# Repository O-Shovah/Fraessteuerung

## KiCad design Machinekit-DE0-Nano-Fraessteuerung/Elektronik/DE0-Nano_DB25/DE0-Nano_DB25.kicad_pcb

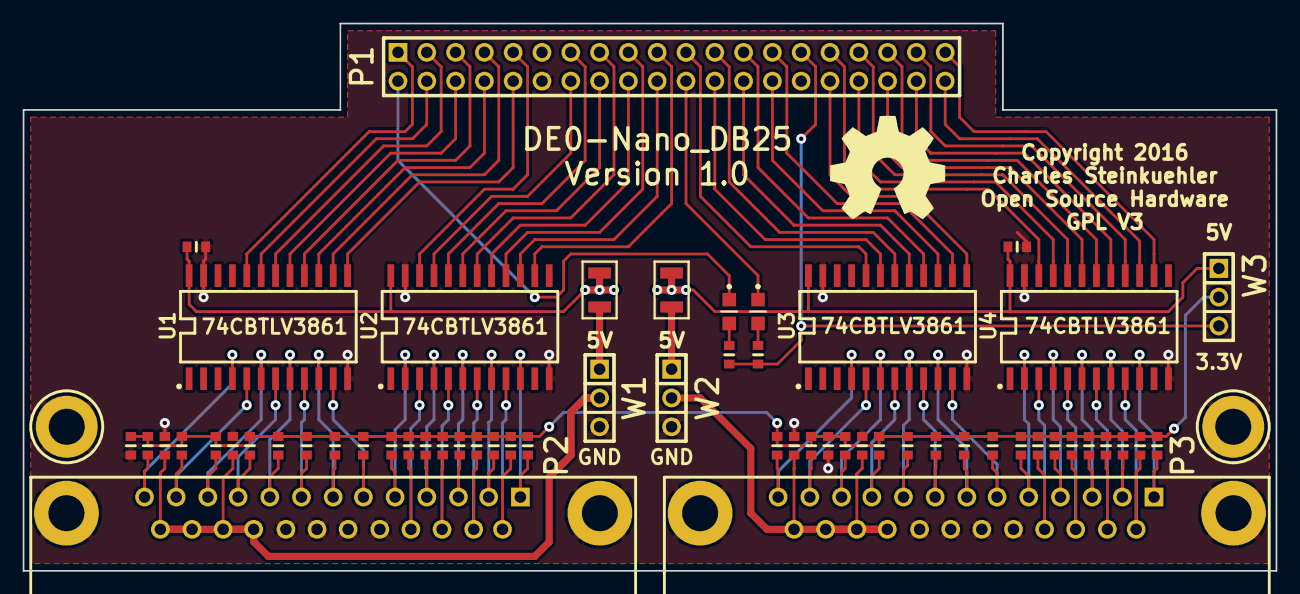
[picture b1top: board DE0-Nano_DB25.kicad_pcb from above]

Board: 2 copper layers, 110.5 x 48.3 mm, 63 parts (0 on the bottom side), 80 nets.

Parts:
C1, C2, C3, C4, C5, C6, C7, C8: 100n; CAPC1608x55N
LED1, LED2: Yellow; OSRAM-LED-0805
M1, M2: 4-40; MTH_4-40
P1: CONN_20X2; Pin_Socket_20x2
P2, P3: DB25; AMP-5747846
PTC1, PTC2: 2A; BOURNS-MF-NSMF
R1, R2, R3, R4, R5, R6, R7, R8, R9, R10, R11, R12, R13, R14, R15, R16, R17, R18, R19, R20, R21, R22, R23, R24, R25, R26, R27, R28, R29, R30, R31, R32, R33, R34: 3.3k; RESC1608x55N
R35, R36: 240R; RESC1608x55N
S1, S2, S3: SHUNT; Shunt
U1, U2, U3, U4: 74CBTLV3861; SOIC127P1030X265-24N
W1, W2, W3: HEADER_3; pin_strip_3

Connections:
+3.3V: P1.29, R35.1, R36.1, W3.3
+5V: C7.1, C8.1, P1.11, PTC1.2, PTC2.2, U1.24, U2.24, U3.24, U4.24, W3.1
/J1-0: P2.1, R1.2, U2.10
/J1-1: P2.14, R2.2, U2.9
/J1-2: P2.2, R3.2, U2.8
/J1-3: P2.15, R4.2, U2.7
/J1-4: P2.3, R5.2, U2.6
/J1-5: P2.16, R6.2, U2.5
/J1-6: P2.4, R7.2, U2.4
/J1-7: P2.17, R8.2, U2.3
/J1-8: P2.5, R9.2, U2.2
/J1-9: P2.6, R10.2, U1.11
/J1-10: P2.7, R11.2, U1.10
/J1-11: P2.8, R12.2, U1.9
/J1-12: P2.9, R13.2, U1.8
/J1-13: P2.10, R14.2, U1.7
/J1-14: P2.11, R15.2, U1.6
/J1-15: P2.12, R16.2, U1.5
/J1-16: P2.13, R17.2, U1.4
/J1-PWR: PTC1.1, W1.1
/J1B0: P1.19, U2.14
/J1B1: P1.20, U2.15
/J1B2: P1.17, U2.16
/J1B3: P1.18, U2.17
/J1B4: P1.15, U2.18
/J1B5: P1.16, U2.19
/J1B6: P1.13, U2.20
/J1B7: P1.14, U2.21
/J1B8: P1.9, U2.22
/J1B9: P1.10, U1.13
/J1B10: P1.7, U1.14
/J1B11: P1.8, U1.15
/J1B12: P1.5, U1.16
/J1B13: P1.6, U1.17
/J1B14: P1.3, U1.18
/J1B15: P1.4, U1.19
/J1B16: P1.1, U1.20
/J2-0: P3.1, R18.2, U4.10
/J2-1: P3.14, R19.2, U4.9
/J2-2: P3.2, R20.2, U4.8
/J2-3: P3.15, R21.2, U4.7
/J2-4: P3.3, R22.2, U4.6
/J2-5: P3.16, R23.2, U4.5
/J2-6: P3.4, R24.2, U4.4
/J2-7: P3.17, R25.2, U4.3
/J2-8: P3.5, R26.2, U4.2
/J2-9: P3.6, R27.2, U3.11
/J2-10: P3.7, R28.2, U3.10
/J2-11: P3.8, R29.2, U3.9
/J2-12: P3.9, R30.2, U3.8
/J2-13: P3.10, R31.2, U3.7
/J2-14: P3.11, R32.2, U3.6
/J2-15: P3.12, R33.2, U3.5
/J2-16: P3.13, R34.2, U3.4
/J2-PWR: PTC2.1, W2.1
/J2B0: P1.39, U4.14
/J2B1: P1.40, U4.15
/J2B2: P1.37, U4.16
/J2B3: P1.38, U4.17
/J2B4: P1.35, U4.18
/J2B5: P1.36, U4.19
/J2B6: P1.33, U4.20
/J2B7: P1.34, U4.21
/J2B8: P1.31, U4.22
/J2B9: P1.32, U3.13
/J2B10: P1.27, U3.14
/J2B11: P1.28, U3.15
/J2B12: P1.25, U3.16
/J2B13: P1.26, U3.17
/J2B14: P1.23, U3.18
/J2B15: P1.24, U3.19
/J2B16: P1.21, U3.20
/LED0: LED1.K, P1.2
/LED1: LED2.K, P1.22
/VPU: C5.1, C6.1, R1.1, R2.1, R3.1, R4.1, R5.1, R6.1, R7.1, R8.1, R9.1, R10.1, R11.1, R12.1, R13.1, R14.1, R15.1, R16.1, R17.1, R18.1, R19.1, R20.1, R21.1, R22.1, R23.1, R24.1, R25.1, R26.1, R27.1, R28.1, R29.1, R30.1, R31.1, R32.1, R33.1, R34.1, W3.2
GND: C1.2, C2.2, C3.2, C4.2, C5.2, C6.2, C7.2, C8.2, M1.1, M2.1, P1.12, P1.30, P2.18, P2.19, P2.20, P2.21, P3.18, P3.19, P3.20, P3.21, U1.12, U1.23, U2.12, U2.23, U3.12, U3.23, U4.12, U4.23, W1.3, W2.3
unnamed: C3.1, C4.1, P3.22, P3.23, P3.24, P3.25, W2.2
unnamed: LED1.A, R35.2
unnamed: LED2.A, R36.2
unnamed: C1.1, C2.1, P2.22, P2.23, P2.24, P2.25, W1.2

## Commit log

2017-03-07 Initial commit with new sorting.
2017-03-07 added Linuxcnc folder.
2017-03-20 Added Linuxcnc branch of the W-Bau machine.
2017-03-22 Added simple M6 reconfiguration. Automatic tool length compensation ist working now.
2019-01-13 Added rack toolchanger test folder.
2019-07-11 Neuer Ordneraufbau fuer bessere integration.
2019-07-12 Orderaufbau neu Strukturiert. Aufgeteilt in einzelne Submaschinen in der Allgemeinen Standardstruktur. Werkzeuglaengensernsor ueberarbeitet und als vollstaendig funktionsfaehig eingestuft.
2019-07-13 Werkzeuglaengensensror dateinamen korrigiert. PYVCP eingebunden und getestet.
2019-07-14 Compile fuer den xhc-whb04b-6 port nach linuxcnc auf 2.7.12 gefahren. Binaerdatei im neuen Ordner auxiliaries abgelegt.
2019-07-14 Neue Konfiguration für Handrad. Handrad und Werkzeuglängensensor auseinandersortiert.
2019-07-14 Readme angepasst.
2019-07-14 ` statt . im Readme
2019-07-15 Handrad funktioniert. Grusaetzlich einsatzbereit.
2019-08-05 Umbau Messzyklus. Abfang erstwerkzeug.
2019-08-05 Werzeuglaenge kompensiert jetzt korrekt.
2019-11-06 Stand vor dem einbau der Probe software
2019-11-07 changed tool meassuerement config part wise.
2019-11-07 First version of manual_toolchange to be tested.
2019-11-07 Umgebaute Steuerung. Werkezugwechsel funktioniert nach bisheriger Erkenntnis.
2019-11-08 Erprobte Version der Werkzeugmlängenmessung. 3D taster implementiert testweise.
2019-11-11 Configs in Regulären Betrieb kopiert. Anpassung der Struktur folgt.
2019-11-11 Neue Version zum Cleanup angelegt. Aufteilung der Funktionen in einzelne Blöcke.
2019-11-12 Adapted Cleanup version for modular ini und hal files.
2019-11-13 Neuer subordner Cleanup-2. Linuxcnc.var als wichtiger Call in der Ini identifiziert.
2019-11-13 Angepasstes Setup in Cleanup. Hal Bauteile verlegt in subfiles.
2019-11-13 Portierung Spindel Signale.
2019-11-14 Anpassungen ini. Vereinheitlichungen signale und Netze
2019-11-14 Lauffähige version mit M6 mit neuem Z Sensor und Handrad :)
2019-11-15 Einsatzerprobung gestartet. Dafür Celanup version kopiert.
2019-11-15 Erfolgreich getestete Condfig der Einsatzerprobung. Fehlerkorreturen in der spindelansteuerung
2019-11-22 Kühlung wird jetzt vor werkzeugwechsel dekativiert.
2019-11-22 Neuer Ordner zur Integration der Python prolog und epilog programme.
2019-11-23 Werkzeugwechsel um korrekte fortsetzung des Ablaufprogramms bie gleichem Werkzeug ergänzt. Python skript implementiert in zweiten branch und angepasst an Erprobungsstand.

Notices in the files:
Machinekit-DE0-Nano-Fraessteuerung/Elektronik/DE0-Nano_DB25/DE0-Nano_DB25.kicad_pcb:
Copyright 2016
GPL V3
